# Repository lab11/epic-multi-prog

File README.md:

Epic Multi Prog
===============

[

](https://raw.github.com/lab11/epic-multi-prog/master/media/epic_multi_prog.jpg)
[

](https://raw.github.com/lab11/epic-multi-prog/master/media/epic_multi_prog_connected.jpg)

Programmer hardware for programming the epic family of devices.
Over the years many different physical connections for programming the epic chip have
been created. This programmer tries to support the common ones:

- Edge style: as used by the Irene family of sensor nodes
- Tag connect (pogo pins): new 6-pin connector from Tag Connect
- Mini prog: 6 pin 2mm connector as used by some epic devices
- Pseudo USB: micro USB connector that also uses the shield for some epic devices

All connection types have their own charging module and charging LED. The center switch
selects which header is connected to the programming lines and therefore which one should
be programmed. The board connects to a computer via a micro USB cable.

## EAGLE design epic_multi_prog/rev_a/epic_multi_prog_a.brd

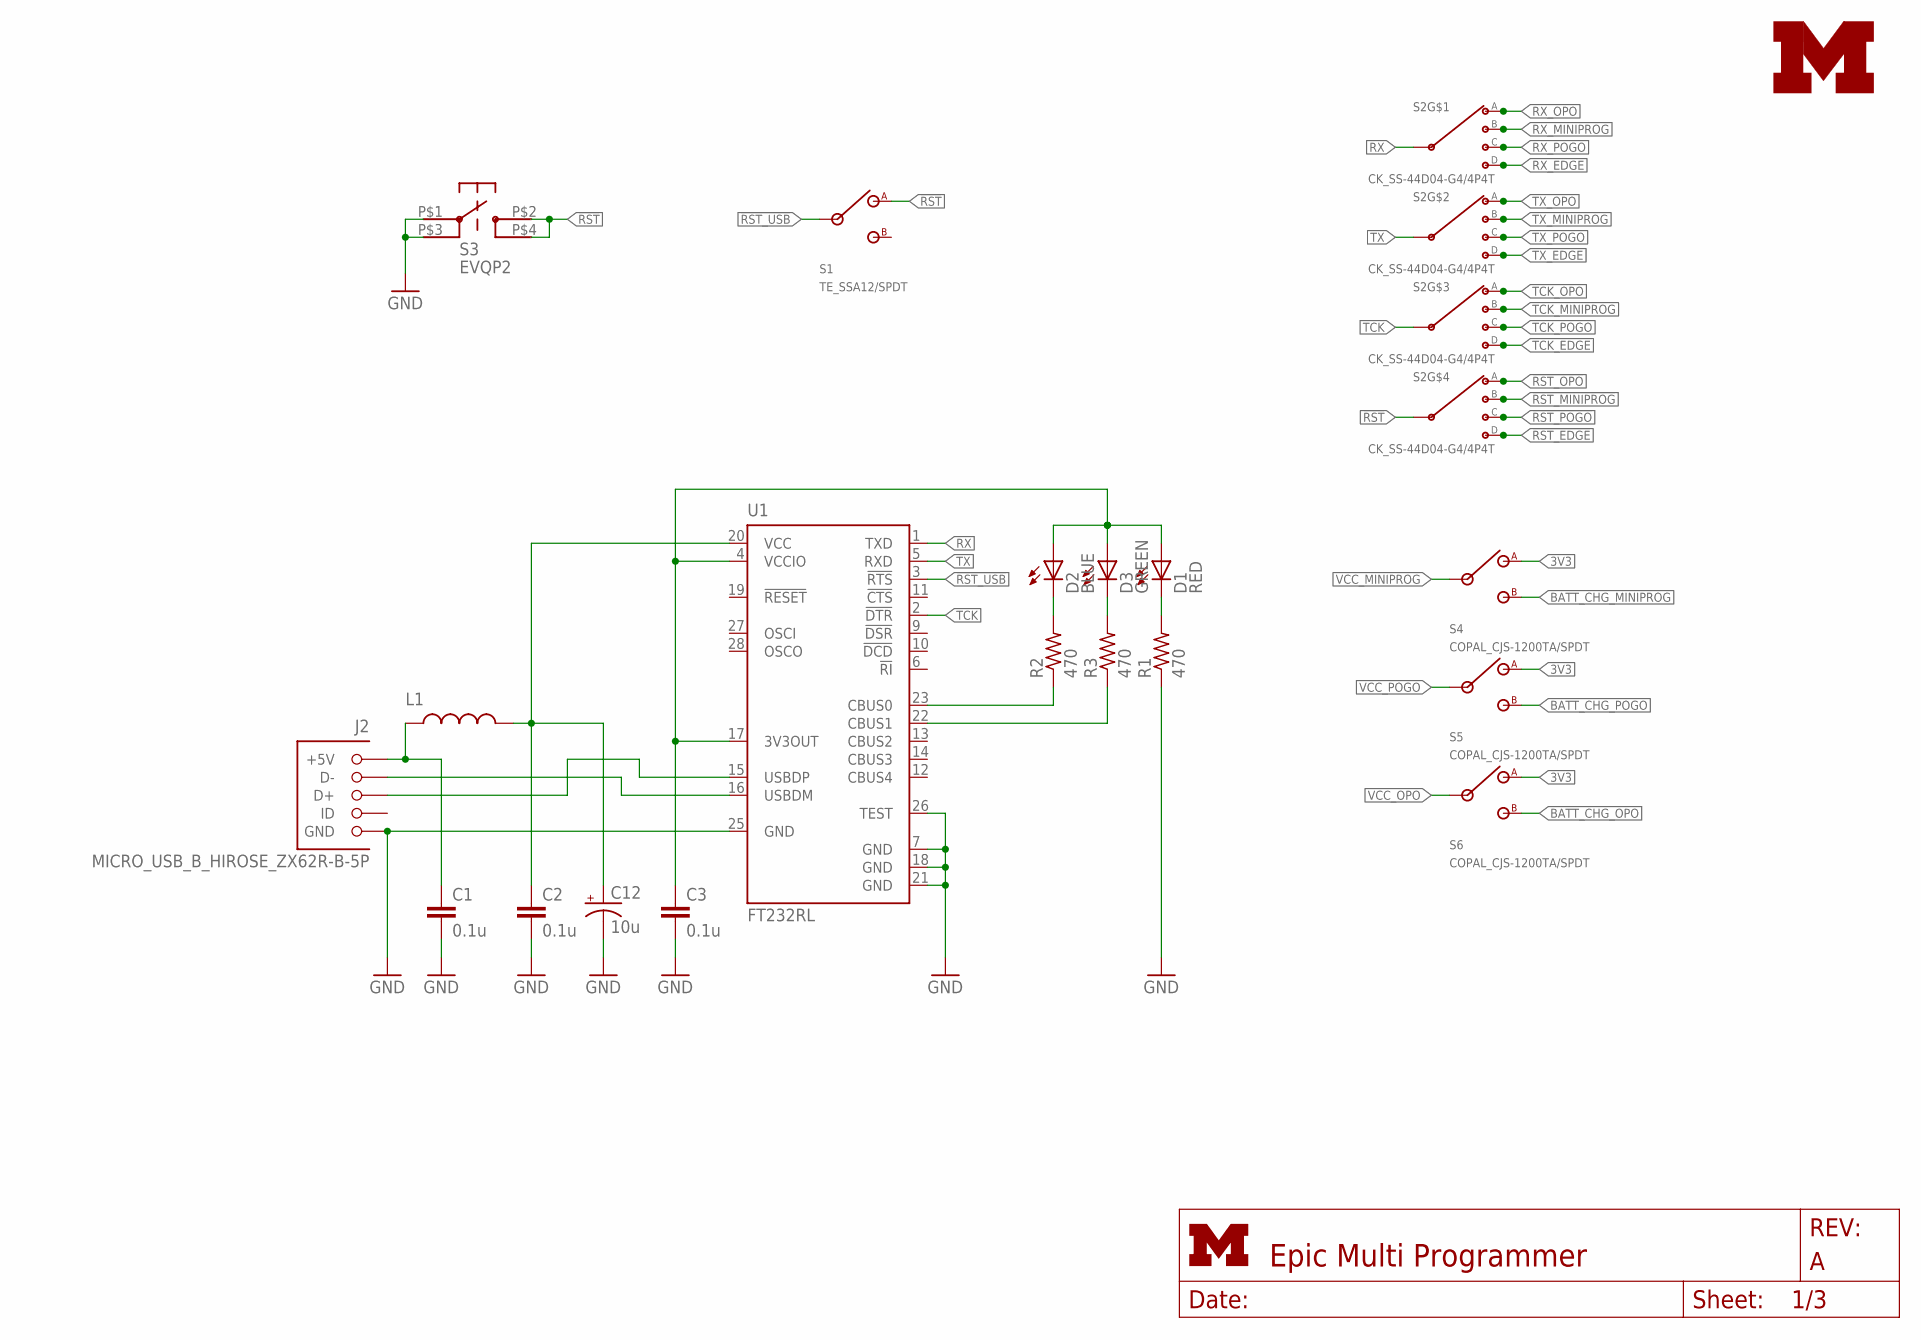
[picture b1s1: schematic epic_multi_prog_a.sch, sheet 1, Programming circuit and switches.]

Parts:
C1, C2, C3: 0.1u; C0603; DIGIKEY 445-1316-1-ND
C12: 10u; EIA3216; DIGIKEY 478-1655-1-ND
D1: RED; LED-0603
D2: BLUE; LED-0603
D3: GREEN; LED-0603
J2: MICRO_USB_B_HIROSE_ZX62R-B-5P; USB_MICRO_B-HIROSE-ZX62R-B-5P
L1: INDUCTOR0603; 0603; DIGIKEY 240-2373-1-ND
R1, R2, R3: 470; R0603
S1: TE_SSA12/SPDT
S2: CK_SS-44D04-G4/4P4T; DIGIKEY CKN10389-ND
S3: EVQP2; DIGIKEY P11084SCT-ND
S4, S5, S6: COPAL_CJS-1200TA/SPDT
U1: FT232RL; SSOP28; DIGIKEY 768-1007-1-ND
U$1: UMICH_SOLID_SMALL; UMICH_SOLID_75MIL

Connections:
3V3: C3.1, D1.A, D2.A, D3.A, S4.2 (A), S5.2 (A), S6.2 (A), U1.4 (VCCIO), U1.17 (3V3OUT); also elsewhere on the board
!RST: S1.1 (A), S2.IND (INPUT), S3.P$2, S3.P$4
!RST_EDGE: S2.D4 (D); also elsewhere on the board
!RST_MINIPROG: S2.D2 (B); also elsewhere on the board
!RST_OPO: S2.D1 (A); also elsewhere on the board
!RST_POGO: S2.D3 (C); also elsewhere on the board
!RST_USB: S1.IN, U1.3 (!RTS)
BATT_CHG_MINIPROG: S4.1 (B); also elsewhere on the board
BATT_CHG_OPO: S6.1 (B); also elsewhere on the board
BATT_CHG_POGO: S5.1 (B); also elsewhere on the board
GND: C1.2, C2.2, C3.2, C12.C (-), J2.5 (GND), R1.1, S3.P$1, S3.P$3, U1.7 (GND), U1.18 (GND), U1.21 (GND), U1.25 (GND), U1.26 (TEST); also elsewhere on the board
unnamed: D2.C, R2.2
unnamed: J2.2 (D-), U1.16 (USBDM)
unnamed: J2.3 (D+), U1.15 (USBDP)
unnamed: C2.1, C12.A (+), L1.2, U1.20 (VCC)
unnamed: D3.C, R3.2
unnamed: D1.C, R1.2
unnamed: R2.1, U1.23 (CBUS0)
unnamed: R3.1, U1.22 (CBUS1)
RX: S2.INA (INPUT), U1.1 (TXD)
RX_EDGE: S2.A4 (D); also elsewhere on the board
RX_MINIPROG: S2.A2 (B); also elsewhere on the board
RX_OPO: S2.A1 (A); also elsewhere on the board
RX_POGO: S2.A3 (C); also elsewhere on the board
TCK: S2.INC (INPUT), U1.2 (!DTR)
TCK_EDGE: S2.C4 (D); also elsewhere on the board
TCK_MINIPROG: S2.C2 (B); also elsewhere on the board
TCK_OPO: S2.C1 (A); also elsewhere on the board
TCK_POGO: S2.C3 (C); also elsewhere on the board
TX: S2.INB (INPUT), U1.5 (RXD)
TX_EDGE: S2.B4 (D); also elsewhere on the board
TX_MINIPROG: S2.B2 (B); also elsewhere on the board
TX_OPO: S2.B1 (A); also elsewhere on the board
TX_POGO: S2.B3 (C); also elsewhere on the board
USB5V: C1.1, J2.1 (+5V), L1.1; also elsewhere on the board
VCC_MINIPROG: S4.IN; also elsewhere on the board
VCC_OPO: S6.IN; also elsewhere on the board
VCC_POGO: S5.IN; also elsewhere on the board

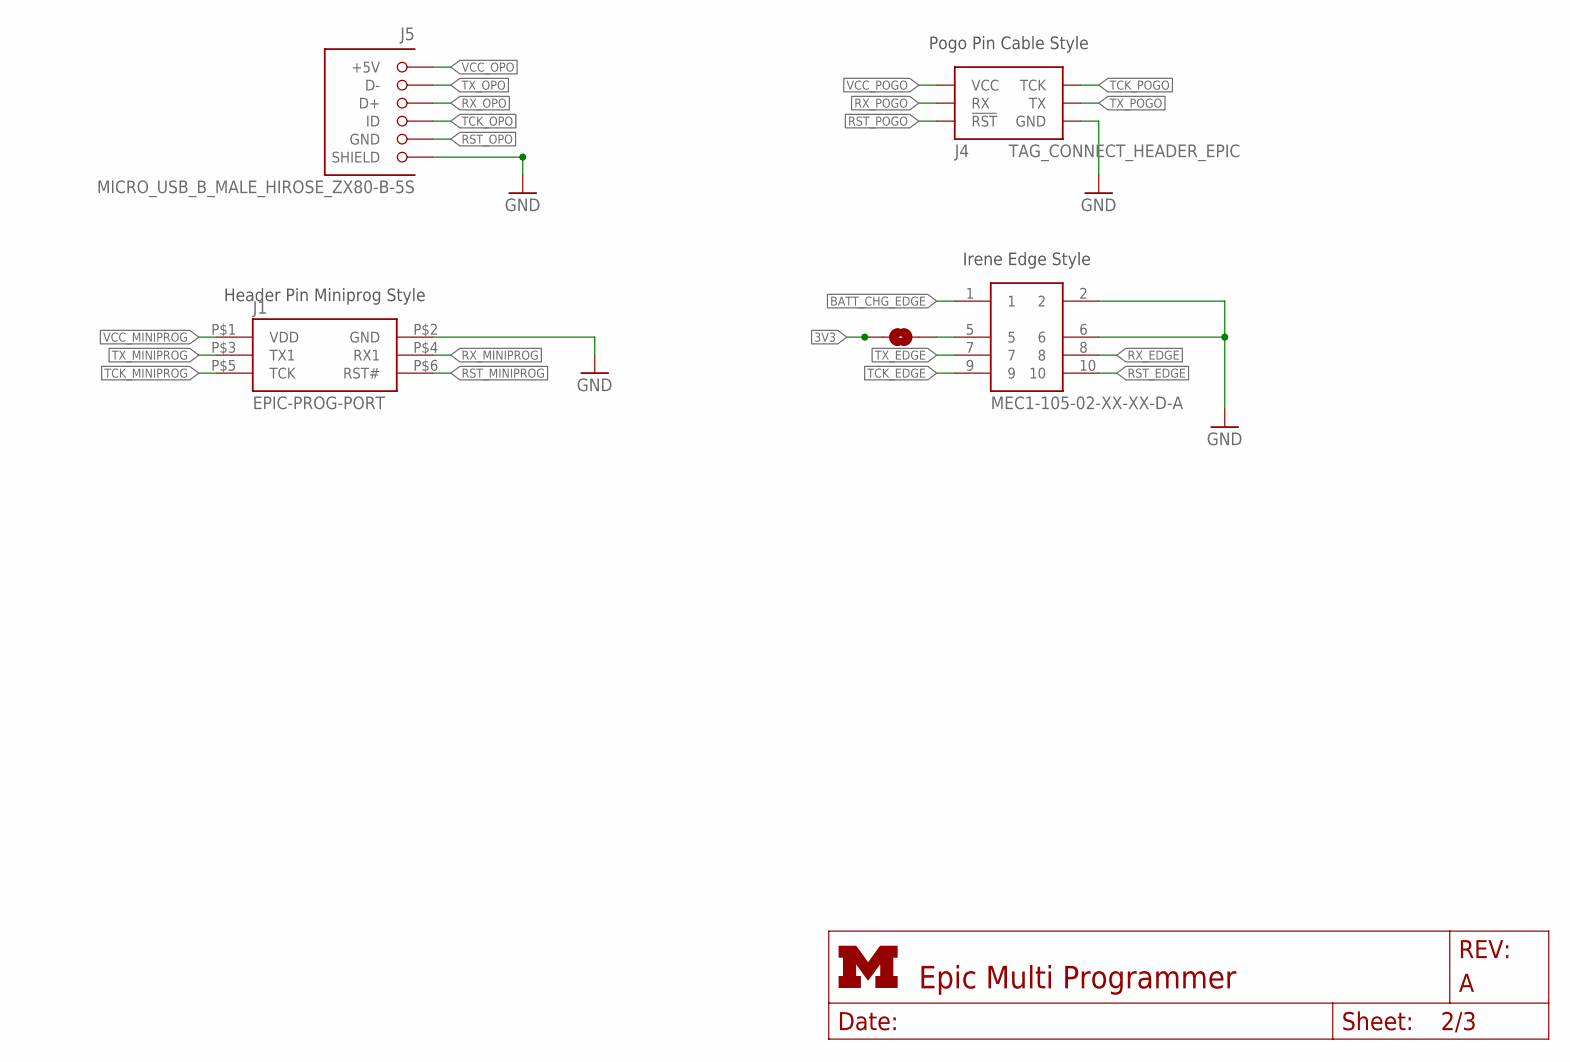
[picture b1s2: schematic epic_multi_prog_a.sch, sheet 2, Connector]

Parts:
J1: EPIC-PROG-PORT; HEADER2X3X2MM
J3: MEC1-105-02-XX-XX-D-A; DIGIKEY SAM8115-ND
J4: TAG_CONNECT_HEADER_EPIC; 2X3_MALE_SHROUDED_0.100
J5: MICRO_USB_B_MALE_HIROSE_ZX80-B-5S; USB_MICRO_B_MALE-HIROSE-ZX80-B-5S; MOUSER 798-ZX80-B-5S
SJ1: SOLDERJUMPERNO; SJ_2S-NO

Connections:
3V3: SJ1.1; also elsewhere on the board
!RST_EDGE: J3.10; also elsewhere on the board
!RST_MINIPROG: J1.P$6 (RST#); also elsewhere on the board
!RST_OPO: J5.5 (GND); also elsewhere on the board
!RST_POGO: J4.6 (!RST); also elsewhere on the board
BATT_CHG_EDGE: J3.1; also elsewhere on the board
GND: J1.P$2 (GND), J3.2, J3.6, J4.2 (GND), J5.SHIELD1 (SHIELD), J5.SHIELD2 (SHIELD), J5.SHIELD3 (SHIELD), J5.SHIELD4 (SHIELD); also elsewhere on the board
unnamed: J3.5, SJ1.2
RX_EDGE: J3.8; also elsewhere on the board
RX_MINIPROG: J1.P$4 (RX1); also elsewhere on the board
RX_OPO: J5.3 (D+); also elsewhere on the board
RX_POGO: J4.4 (RX); also elsewhere on the board
TCK_EDGE: J3.9; also elsewhere on the board
TCK_MINIPROG: J1.P$5 (TCK); also elsewhere on the board
TCK_OPO: J5.4 (ID); also elsewhere on the board
TCK_POGO: J4.5 (TCK); also elsewhere on the board
TX_EDGE: J3.7; also elsewhere on the board
TX_MINIPROG: J1.P$3 (TX1); also elsewhere on the board
TX_OPO: J5.2 (D-); also elsewhere on the board
TX_POGO: J4.3 (TX); also elsewhere on the board
VCC_MINIPROG: J1.P$1 (VDD); also elsewhere on the board
VCC_OPO: J5.1 (+5V); also elsewhere on the board
VCC_POGO: J4.1 (VCC); also elsewhere on the board

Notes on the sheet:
Irene Edge Style
Header Pin Miniprog Style
Pogo Pin Cable Style

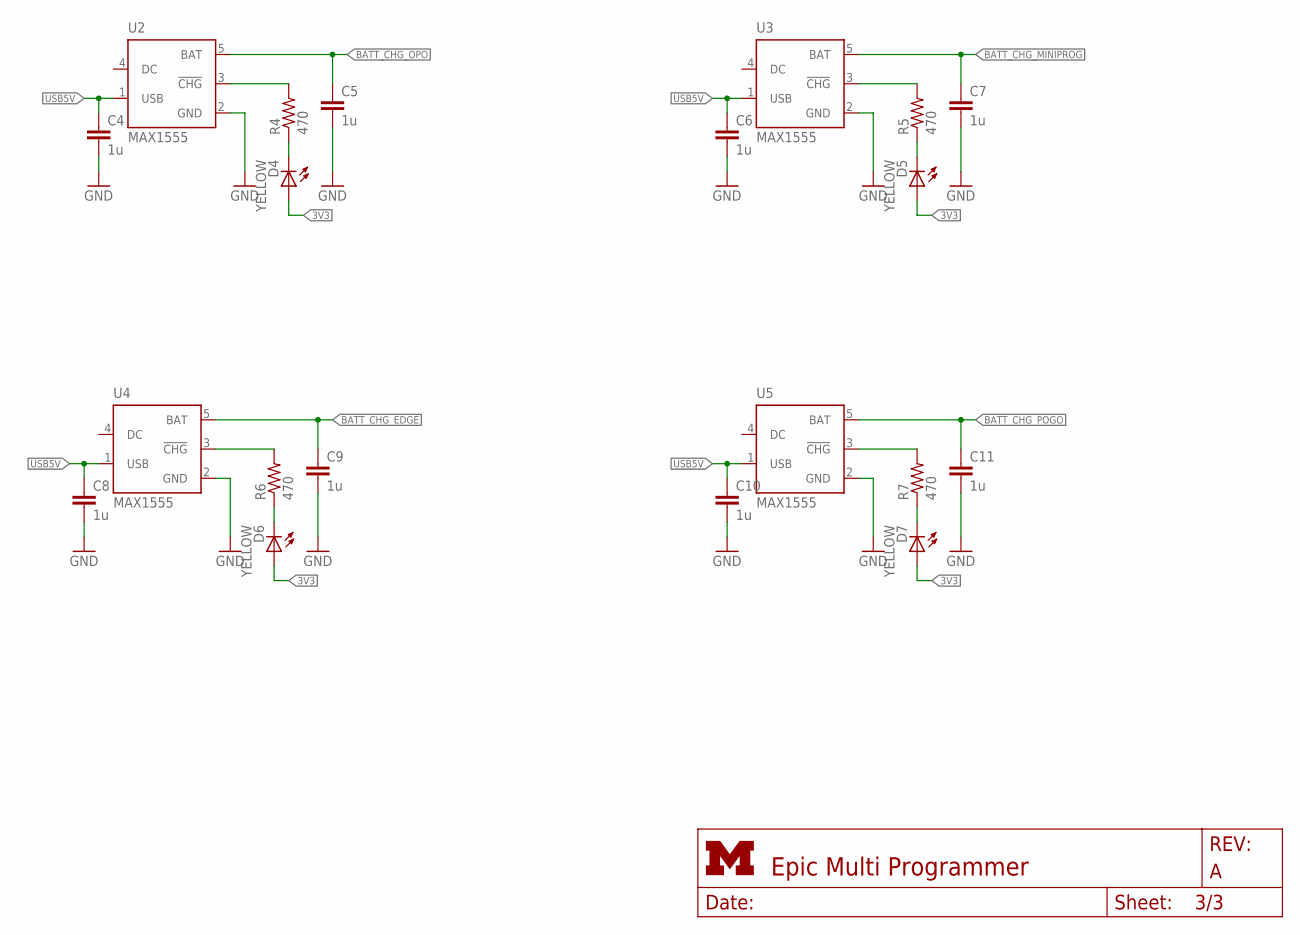
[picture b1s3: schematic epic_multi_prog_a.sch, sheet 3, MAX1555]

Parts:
C4, C5, C6, C7, C8, C9, C10, C11: 1u; C0603; DIGIKEY 445-1321-1-ND
D4, D5, D6, D7: YELLOW; LED-0603
R4, R5, R6, R7: 470; R0603
U2, U3, U4, U5: MAX1555; SOT23-5L; DIGIKEY MAX1555EZK+TCT-ND

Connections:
3V3: D4.A, D5.A, D6.A, D7.A; also elsewhere on the board
BATT_CHG_EDGE: C9.1, U4.5 (BAT); also elsewhere on the board
BATT_CHG_MINIPROG: C7.1, U3.5 (BAT); also elsewhere on the board
BATT_CHG_OPO: C5.1, U2.5 (BAT); also elsewhere on the board
BATT_CHG_POGO: C11.1, U5.5 (BAT); also elsewhere on the board
GND: C4.2, C5.2, C6.2, C7.2, C8.2, C9.2, C10.2, C11.2, U2.2 (GND), U3.2 (GND), U4.2 (GND), U5.2 (GND); also elsewhere on the board
unnamed: D5.C, R5.1
unnamed: D4.C, R4.1
unnamed: R4.2, U2.3 (!CHG)
unnamed: R5.2, U3.3 (!CHG)
unnamed: D6.C, R6.1
unnamed: R6.2, U4.3 (!CHG)
unnamed: D7.C, R7.1
unnamed: R7.2, U5.3 (!CHG)
USB5V: C4.1, C6.1, C8.1, C10.1, U2.1 (USB), U3.1 (USB), U4.1 (USB), U5.1 (USB); also elsewhere on the board

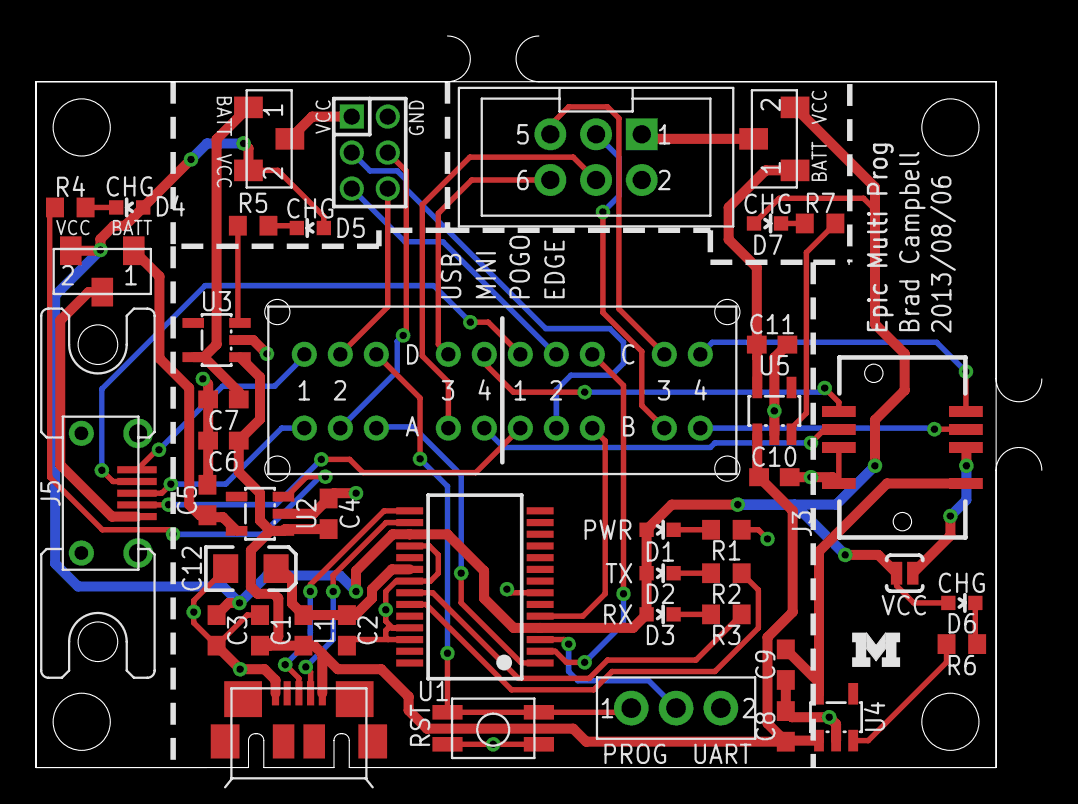
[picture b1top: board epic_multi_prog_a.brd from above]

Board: 2 copper layers, 55.9 x 40.6 mm, 45 parts (0 on the bottom side), 48 nets.

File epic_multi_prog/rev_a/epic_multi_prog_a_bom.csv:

# Bill of Materials
# Converted from epic_multi_prog_a_bom.xls
# Generated by bom_to_text.py

Qty,Value,Device,Package,Parts,Description,DIGIKEY,MOUSER
3,0.1u,C-EUC0603,C0603,"C1, C2, C3","CAPACITOR, European symbol",445-1316-1-ND,
8,1u,C-EUC0603,C0603,"C4, C5, C6, C7, C8, C9, C10, C11","CAPACITOR, European symbol",445-1321-1-ND,
1,10u,CAP_POL1206,EIA3216,C12,Capacitor Polarized,478-1655-1-ND,
1,BLUE,LED0603,LED-0603,D1,LEDs,160-1837-6-ND,
1,RED,LED0603,LED-0603,D2,LEDs,160-1835-6-ND,
1,GREEN,LED0603,LED-0603,D3,LEDs,160-1834-6-ND,
4,YELLOW,LED0603,LED-0603,"D4, D5, D6, D7",LEDs,160-1184-6-ND,
1,EPIC-PROG-PORT,EPIC-PROG-PORT,HEADER2X3X2MM,J1,,3M9173-ND,
1,MICRO_USB_B_HIROSE_ZX62R-B-5P,MICRO_USB_B_HIROSE_ZX62R-B-5P,USB_MICRO_B-HIROSE-ZX62R-B-5P,J2,USB Micro B Connector,H11574CT-ND,
1,MEC1-105-02-XX-XX-D-A,MEC1-105-02-XX-XX-D-A,MEC1-105-02-XX-XX-D-A,J3,,SAM8115-ND,
1,TAG_CONNECT_HEADER_EPIC,TAG_CONNECT_HEADER_EPIC,2X3_MALE_SHROUDED_0.100,J4,2x3 Male Shrouded Header 0.100,3M15451-ND,
1,MICRO_USB_B_MALE_HIROSE_ZX80-B-5S,MICRO_USB_B_MALE_HIROSE_ZX80-B-5S,USB_MICRO_B_MALE-HIROSE-ZX80-B-5S,J5,CONN PLUG MCR USB B PCB VERT,H11612-ND,798-ZX80-B-5S
1,,INDUCTOR0603,603,L1,Inductors,240-2373-1-ND,
7,470,R-US_R0603,R0603,"R1, R2, R3, R4, R5, R6, R7","RESISTOR, American symbol",P470GDKR-ND,
1,TE_SSA12/SPDT,TE_SSA12/SPDT,TE_SSA12/SPDT,S1,SWITCH SLIDE SPDT 2POS SSA SER,450-1602-ND,
1,CK_SS-44D04-G4/4P4T,CK_SS-44D04-G4/4P4T,CK_SS-44D04-G4/4P4T,S2,Through hole 4P4T switch.,CKN10389-ND,
1,EVQP2,EVQP2,EVQP2,S3,,P11084SCT-ND,
3,COPAL_CJS-1200TA/SPDT,COPAL_CJS-1200TA/SPDT,COPAL_CJS-1200TA/SPDT,"S4, S5, S6",SWITCH SLIDE SPDT SMD J-LEAD,563-1021-2-ND,
1,FT232RL,FT232RL,SSOP28,U1,FTDI chip,768-1007-1-ND,
4,MAX1555,MAX1555,SOT23-5L,"U2, U3, U4, U5",Dual-Input USB/AC Adapter 1-Cell Li+ Battery Chargers,MAX1555EZK+TCT-ND,

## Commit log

2013-07-14 Start on the universal programmer board for epic
2013-07-14 Test routing to see how this board is going to look
2013-07-14 added power switches, moving things around
2013-07-14 Moved uart/prog switch
    Planning on the huge smd micro usb
2013-07-14 Moved ftdi circuit over to fill space
2013-07-14 Nearly routed, added more max1555s
    Decided that each circuit should have its own charging led.
2013-07-14 Cleaned up airwires
    Need to get the pinout for programming opo.
2013-07-15 added bom
2013-07-22 added opo usb connection
2013-07-22 added milling layer for pannelization
2013-08-06 updated epic multi prog to ship
    Checked bom, double checked opo, changed date.
2013-08-16 gitignore for eagle and whatnot
2013-08-16 added images and better readme
2013-08-16 fixed filename
2013-08-16 smaller image
2013-08-16 epic multi prog pdf and gerbs
2013-09-03 added full zip
2013-09-04 new bom
2013-09-13 updated bom
2013-09-13 running eagle script
2013-10-02 new epic multip prog zip
2014-01-09 better doc for pcb

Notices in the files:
parts and their libraries:
SparkFun: Licensing: CC v3.0 Share-Alike You are welcome to use this library for commercial purposes.
